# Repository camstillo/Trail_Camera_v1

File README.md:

# Trail_Camera_v1
 Schematic and ordering information for trail camera device

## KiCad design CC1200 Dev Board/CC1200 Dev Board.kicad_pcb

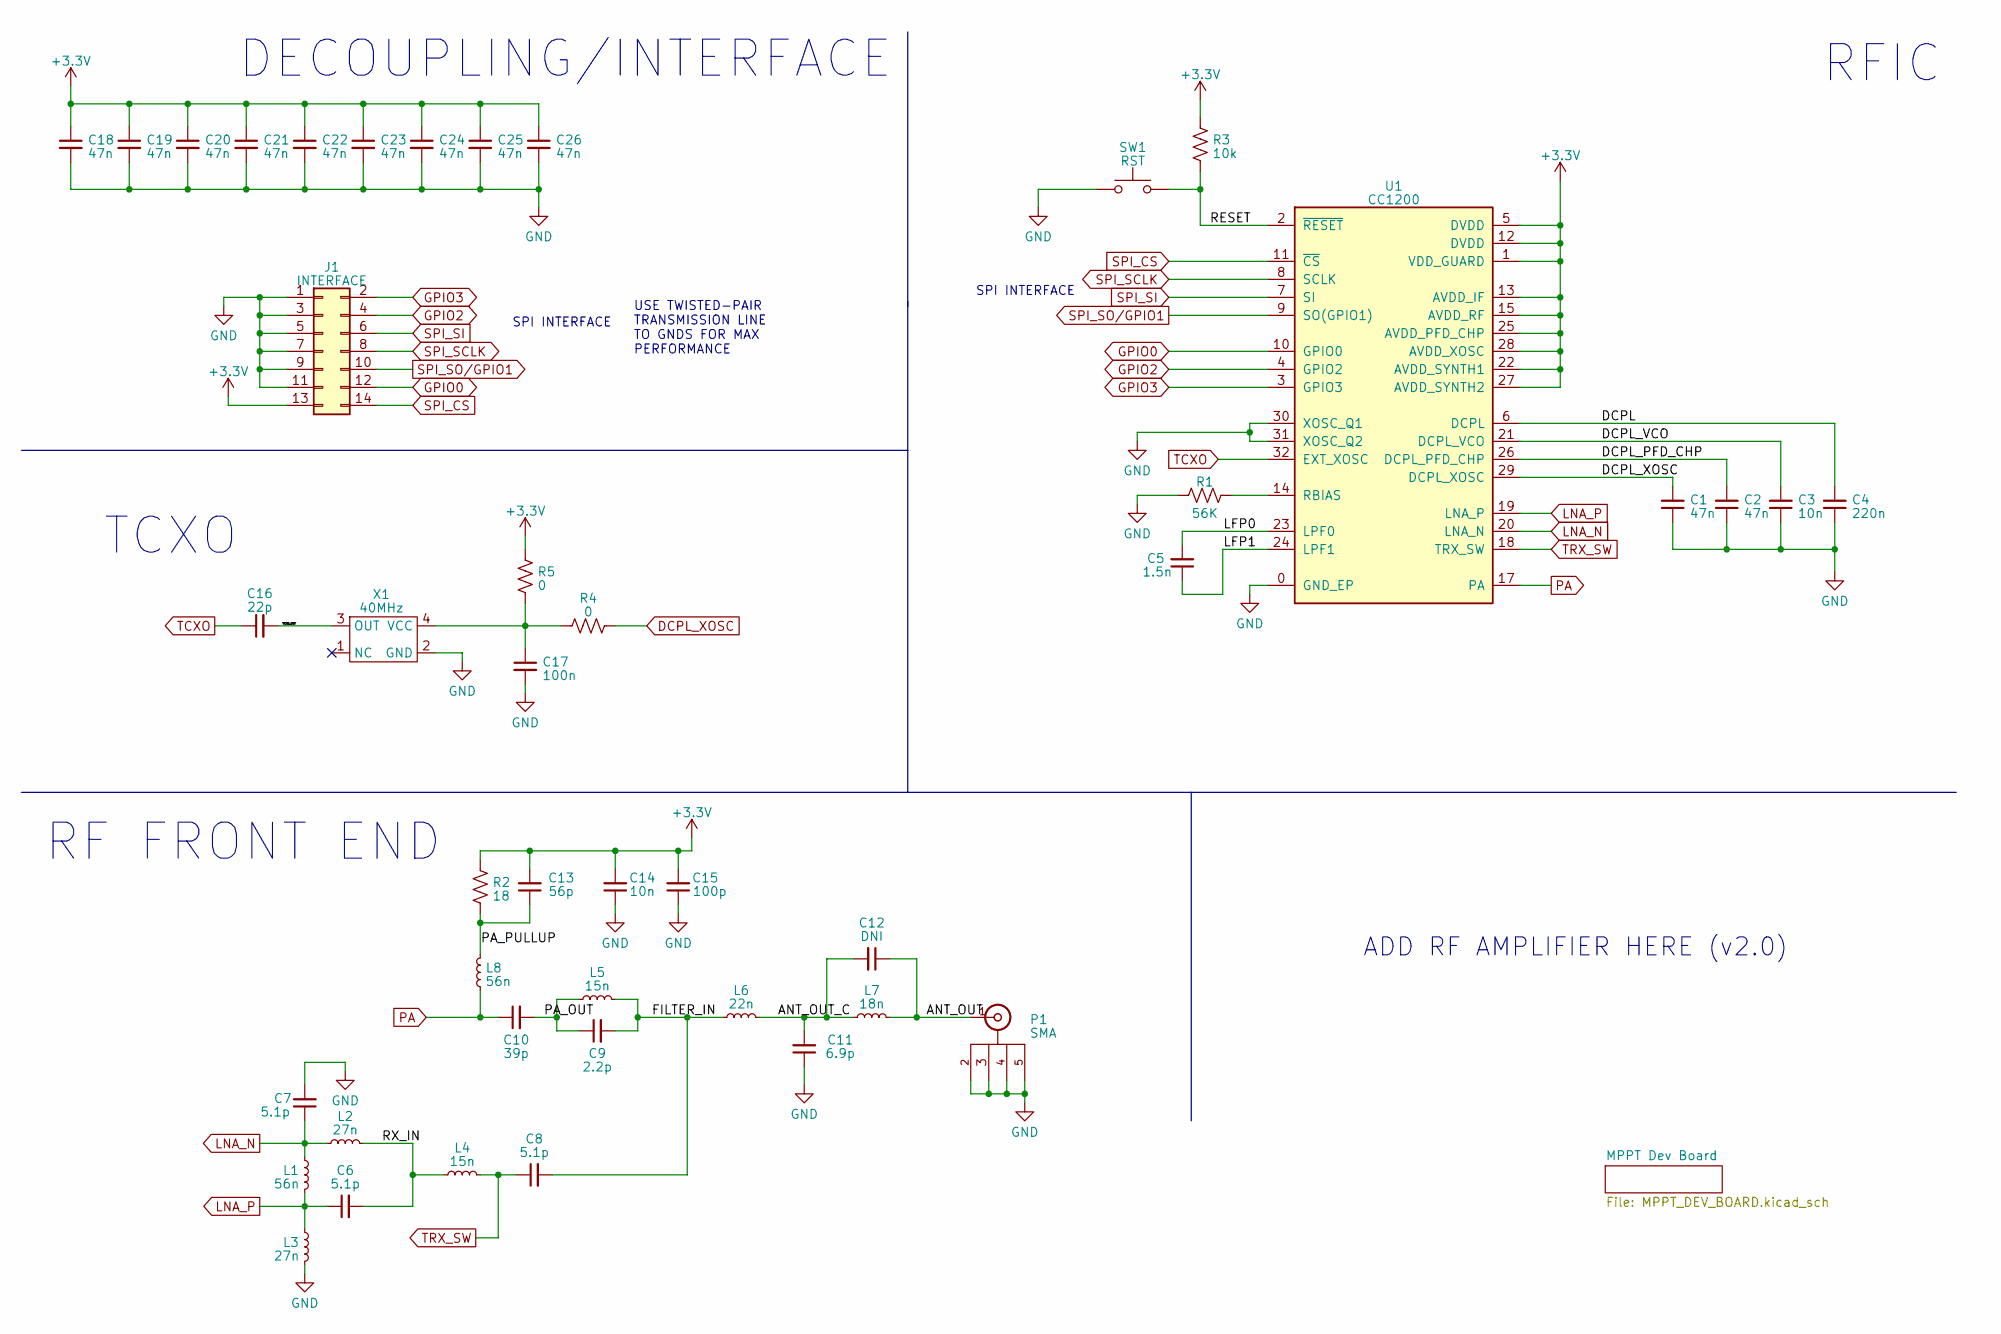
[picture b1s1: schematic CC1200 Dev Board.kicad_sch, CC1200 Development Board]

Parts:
C1, C2, C18, C19, C20, C21, C22, C23, C24, C25, C26: 47n; C_0402_1005Metric_Pad0.74x0.62mm_HandSolder
C3, C14: 10n; C_0402_1005Metric_Pad0.74x0.62mm_HandSolder
C4: 220n; C_0402_1005Metric_Pad0.74x0.62mm_HandSolder
C5: 1.5n; C_0402_1005Metric_Pad0.74x0.62mm_HandSolder
C6, C7, C8: 5.1p; C_0402_1005Metric_Pad0.74x0.62mm_HandSolder
C9: 2.2p; C_0402_1005Metric_Pad0.74x0.62mm_HandSolder
C10: 39p; C_0402_1005Metric_Pad0.74x0.62mm_HandSolder
C11: 6.9p; C_0402_1005Metric_Pad0.74x0.62mm_HandSolder
C12: DNI; C_0402_1005Metric_Pad0.74x0.62mm_HandSolder
C13: 56p; C_0402_1005Metric_Pad0.74x0.62mm_HandSolder
C15: 100p; C_0402_1005Metric_Pad0.74x0.62mm_HandSolder
C16: 22p; C_0402_1005Metric_Pad0.74x0.62mm_HandSolder
C17: 100n; C_0402_1005Metric_Pad0.74x0.62mm_HandSolder
J1: INTERFACE; PinHeader_2x07_P2.54mm_Vertical_SMD
L1, L8: 56n; L_0402_1005Metric_Pad0.77x0.64mm_HandSolder
L2, L3: 27n; L_0402_1005Metric_Pad0.77x0.64mm_HandSolder
L4, L5: 15n; L_0402_1005Metric_Pad0.77x0.64mm_HandSolder
L6: 22n; L_0402_1005Metric_Pad0.77x0.64mm_HandSolder
L7: 18n; L_0402_1005Metric_Pad0.77x0.64mm_HandSolder
P1: SMA; CONSMA001-SMD-G_ALT
R1: 56K; R_0402_1005Metric_Pad0.72x0.64mm_HandSolder
R2: 18; R_0402_1005Metric_Pad0.72x0.64mm_HandSolder
R3: 10k; R_0402_1005Metric_Pad0.72x0.64mm_HandSolder
R4, R5: 0; R_0402_1005Metric_Pad0.72x0.64mm_HandSolder
SW1: RST; PTS636 SL43 SMTR LFS
U1: CC1200
X1: 40MHz; TG2520SMN

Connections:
+3.3V: C13.2, C14.2, C15.2, C18.1, C19.1, C20.1, C21.1, C22.1, C23.1, C24.1, C25.1, C26.1, J1.13, R2.1, R3.1, R5.2, U1.1 (VDD_GUARD), U1.5 (DVDD), U1.12 (DVDD), U1.13 (AVDD_IF), U1.15 (AVDD_RF), U1.22 (AVDD_SYNTH1), U1.25 (AVDD_PFD_CHP), U1.27 (AVDD_SYNTH2), U1.28 (AVDD_XOSC)
/ANT_OUT: C12.1, L7.2, P1.1 (In); also elsewhere on the board
/ANT_OUT_C: C11.2, C12.2, L6.2, L7.1
/DCPL: C4.2, U1.6 (DCPL)
/DCPL_PFD_CHP: C2.2, U1.26 (DCPL_PFD_CHP)
/DCPL_VCO: C3.2, U1.21 (DCPL_VCO)
/FILTER_IN: C8.2, C9.2, L5.2, L6.1
/LFP0: C5.2, U1.23 (LPF0)
/LFP1: C5.1, U1.24 (LPF1)
/PA_OUT: C9.1, C10.2, L5.1
/PA_PULLUP: C13.1, L8.2, R2.2
/RESET: R3.2, SW1.2, U1.2 (~RESET); also elsewhere on the board
/RX_IN: C6.2, L2.2, L4.1
/TCXO_OUT: C16.2, X1.3 (OUT)
DCPL_XOSC: C1.2, R4.2, U1.29 (DCPL_XOSC)
GND: C1.1, C2.1, C3.1, C4.1, C7.2, C11.1, C14.1, C15.1, C17.2, C18.2, C19.2, C20.2, C21.2, C22.2, C23.2, C24.2, C25.2, C26.2, J1.1, J1.3, J1.5, J1.7, J1.9, J1.11, L3.2, P1.2 (Body), P1.3, P1.4, P1.5, R1.1, SW1.1, U1.0 (GND_EP), U1.30 (XOSC_Q1), U1.31 (XOSC_Q2), X1.2 (GND); also elsewhere on the board
GPIO0: J1.12, U1.10 (GPIO0)
GPIO2: J1.4, U1.4 (GPIO2)
GPIO3: J1.2, U1.3 (GPIO3)
LNA_N: C7.1, L1.1, L2.1, U1.20 (LNA_N)
LNA_P: C6.1, L1.2, L3.1, U1.19 (LNA_P)
MPPTSET_RST: SW1.2; also elsewhere on the board
unnamed: R1.2, U1.14 (RBIAS)
unnamed: C17.1, R4.1, R5.1, X1.4 (VCC)
PA: C10.1, L8.1, U1.17 (PA)
SPI_CS: J1.14, U1.11 (~CS)
SPI_SCLK: J1.8, U1.8 (SCLK)
SPI_SI: J1.6, U1.7 (SI)
SPI_SO/GPIO1: J1.10, U1.9 (SO(GPIO1))
TCXO: C16.1, U1.32 (EXT_XOSC)
TRX_SW: C8.1, L4.2, U1.18 (TRX_SW)

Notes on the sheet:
RFIC
TCXO
RF FRONT END
ADD RF AMPLIFIER HERE (v2.0)
DECOUPLING/INTERFACE
USE TWISTED-PAIR TRANSMISSION LINE TO GNDS FOR MAX PERFORMANCE
SPI INTERFACE

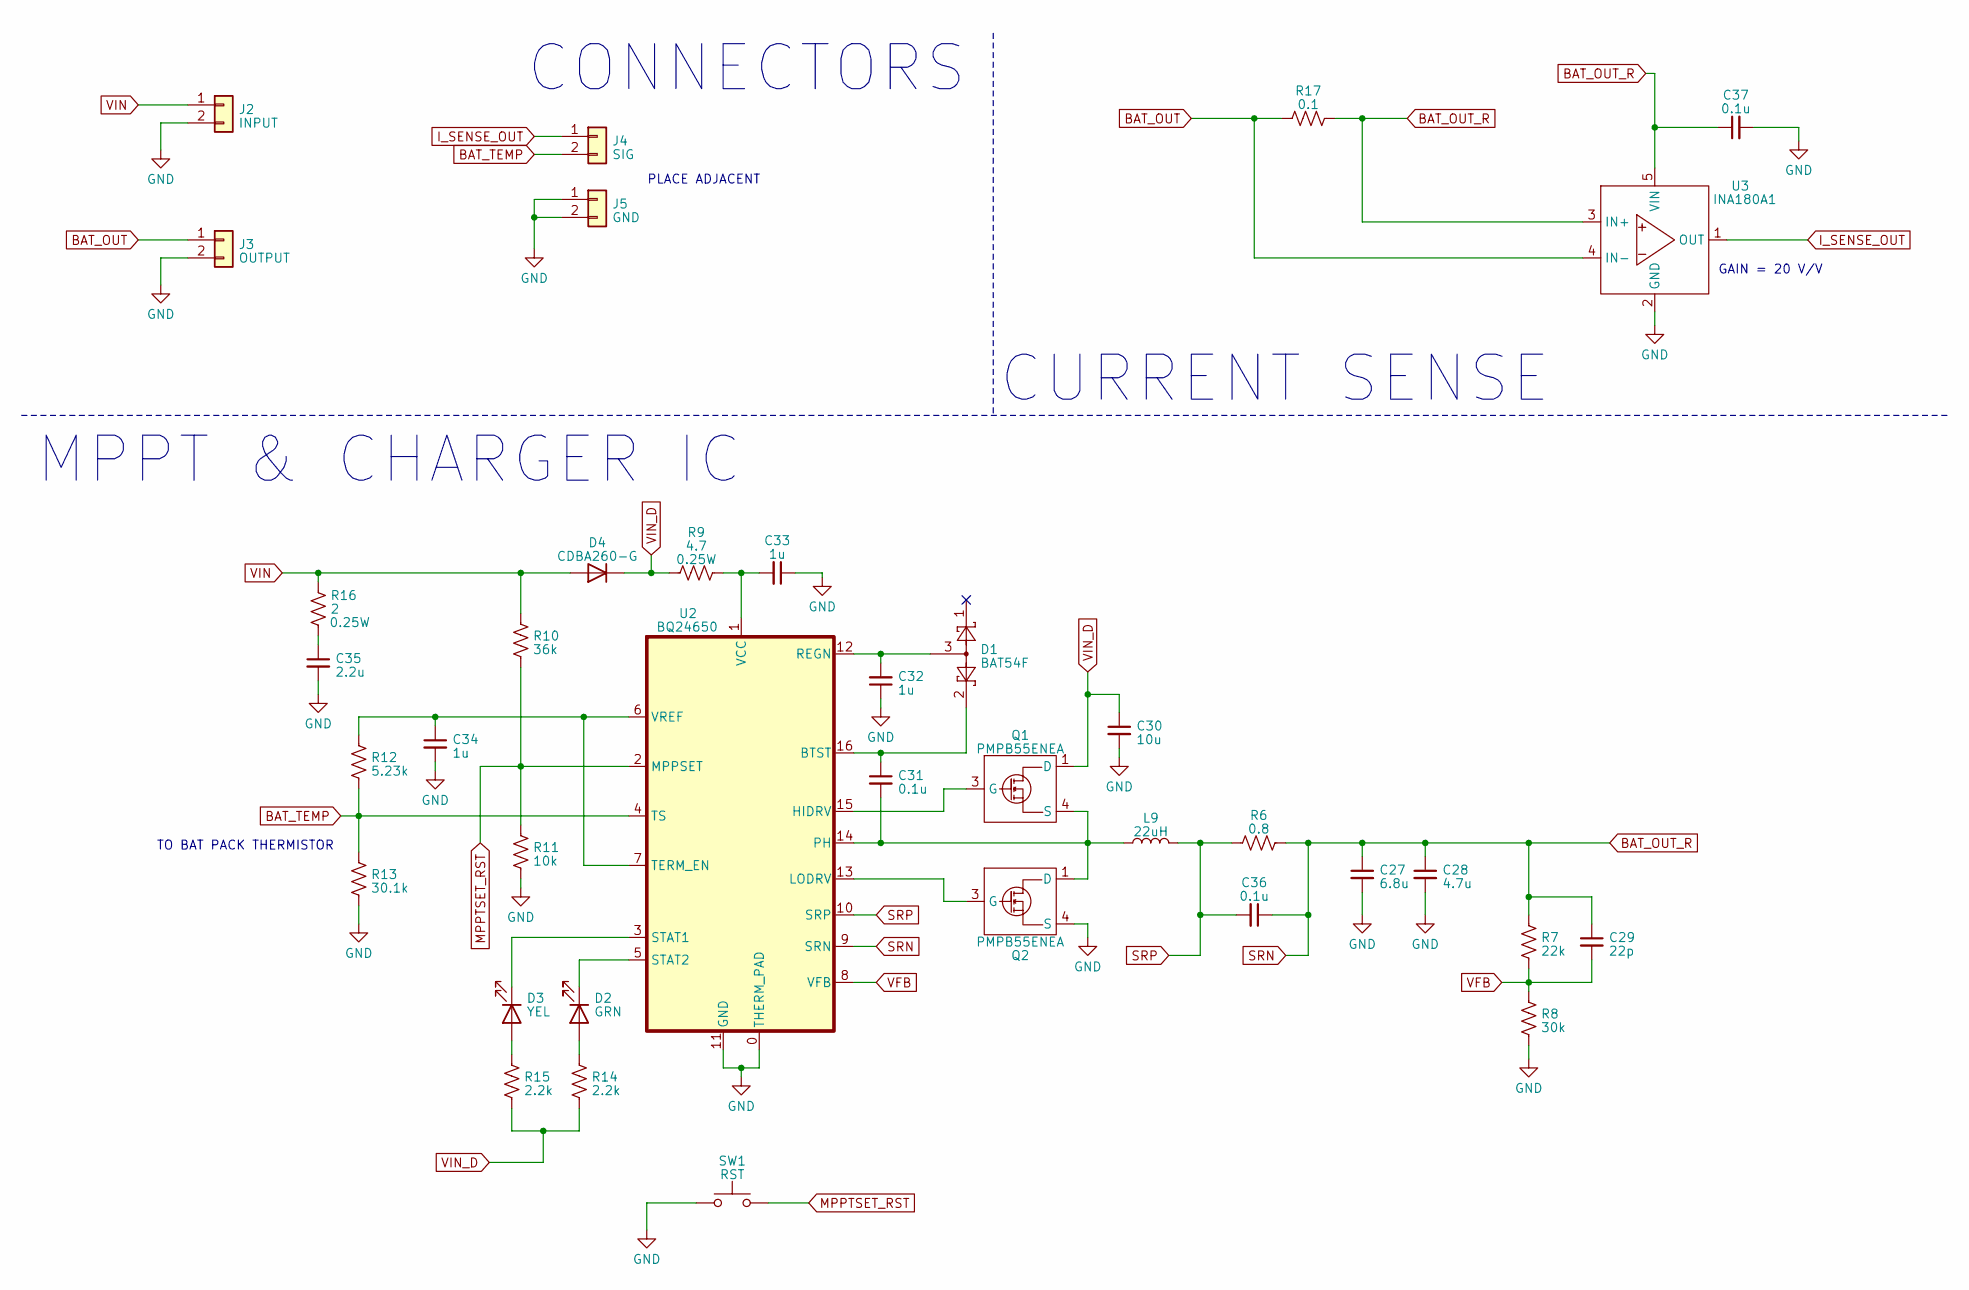
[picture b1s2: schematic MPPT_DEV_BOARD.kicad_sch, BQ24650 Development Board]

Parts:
C27: 6.8u; C_1206_3216Metric
C28: 4.7u; C_1206_3216Metric
C29: 22p; C_0402_1005Metric_Pad0.74x0.62mm_HandSolder
C30: 10u; C_0603_1608Metric
C31, C36, C37: 0.1u; C_0402_1005Metric_Pad0.74x0.62mm_HandSolder
C32, C33, C34: 1u; C_0402_1005Metric_Pad0.74x0.62mm_HandSolder
C35: 2.2u; C_0603_1608Metric
D1: BAT54F; BAT54-7-F
D2: GRN; MSAST105SB5104KFNA01
D3: YEL; MSAST105SB5104KFNA01
D4: CDBA260-G
J2: INPUT; InOut_Pads
J3: OUTPUT; InOut_Pads
J4: SIG; InOut_Pads
J5: GND; InOut_Pads
L9: 22uH; SRR1005-220Y
Q1, Q2: PMPB55ENEA
R6: 0.8; R_1206_3216Metric
R7: 22k; R_0402_1005Metric_Pad0.72x0.64mm_HandSolder
R8: 30k; R_0402_1005Metric_Pad0.72x0.64mm_HandSolder
R9: 4.7; R_1206_3216Metric
R10: 36k; R_0402_1005Metric_Pad0.72x0.64mm_HandSolder
R11: 10k; R_0402_1005Metric_Pad0.72x0.64mm_HandSolder
R12: 5.23k; R_0402_1005Metric_Pad0.72x0.64mm_HandSolder
R13: 30.1k; R_0402_1005Metric_Pad0.72x0.64mm_HandSolder
R14, R15: 2.2k; R_0402_1005Metric_Pad0.72x0.64mm_HandSolder
R16: 2; R_1206_3216Metric
R17: 0.1; R_0603_1608Metric
SW1: RST; PTS636 SL43 SMTR LFS
U2: BQ24650
U3: INA180A1; INA180A1IDBVR

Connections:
/RESET: SW1.2; also elsewhere on the board
BAT_OUT: J3.1, R17.1, U3.4 (IN-)
BAT_OUT_R: C27.1, C28.1, C29.1, C36.1, C37.1, R6.2, R7.2, R17.2, U2.9 (SRN), U3.3 (IN+), U3.5 (VIN)
BAT_TEMP: J4.2, R12.1, R13.2, U2.4 (TS)
GND: C27.2, C28.2, C30.2, C32.1, C33.1, C34.2, C35.2, C37.2, J2.2, J3.2, J5.1, J5.2, Q2.4 (S), Q2.8 (S), R8.1, R11.1, R13.1, SW1.1, U2.0 (THERM_PAD), U2.11 (GND), U3.2 (GND); also elsewhere on the board
I_SENSE_OUT: J4.1, U3.1 (OUT)
MPPTSET_RST: R10.1, R11.2, SW1.2, U2.2 (MPPSET); also elsewhere on the board
unnamed: C35.1, R16.1
unnamed: D2.2 (A), R14.2
unnamed: D2.1 (K), U2.5 (STAT2)
unnamed: D3.2 (A), R15.2
unnamed: D3.1 (K), U2.3 (STAT1)
unnamed: Q1.3 (G), U2.15 (HIDRV)
unnamed: Q2.3 (G), U2.13 (LODRV)
unnamed: C31.1, D1.2, U2.16 (BTST)
unnamed: C31.2, L9.1, Q1.4 (S), Q1.8 (S), Q2.1 (D), Q2.2 (D), Q2.5 (D), Q2.6 (D), Q2.7 (D), U2.14 (PH)
unnamed: C32.2, D1.3, U2.12 (REGN)
unnamed: C34.1, R12.2, U2.6 (VREF), U2.7 (TERM_EN)
unnamed: C33.2, R9.2, U2.1 (VCC)
SRP: C36.2, L9.2, R6.1, U2.10 (SRP)
VFB: C29.2, R7.1, R8.2, U2.8 (VFB)
VIN: D4.2 (A), J2.1, R10.2, R16.2
VIN_D: C30.1, D4.1 (K), Q1.1 (D), Q1.2 (D), Q1.5 (D), Q1.6 (D), Q1.7 (D), R9.1, R14.1, R15.1

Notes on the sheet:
MPPT & CHARGER IC
PLACE ADJACENT
GAIN = 20 V/V
CURRENT SENSE
CONNECTORS
TO BAT PACK THERMISTOR

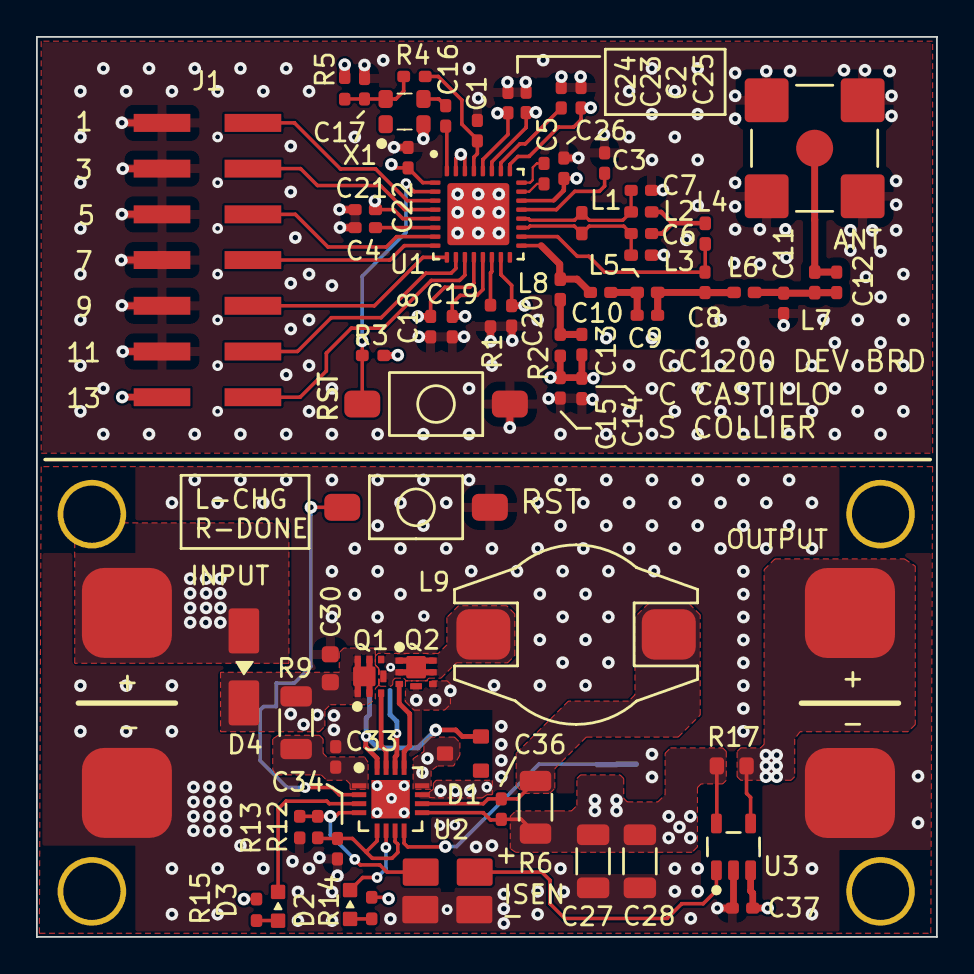
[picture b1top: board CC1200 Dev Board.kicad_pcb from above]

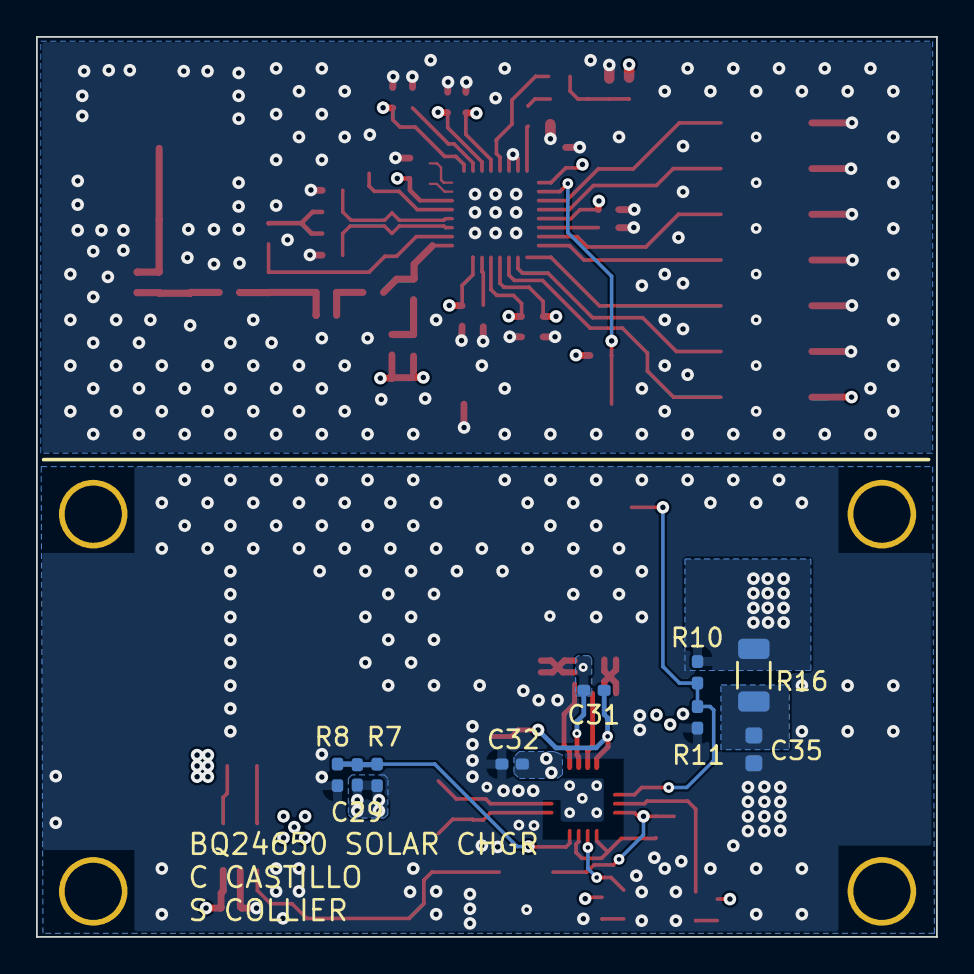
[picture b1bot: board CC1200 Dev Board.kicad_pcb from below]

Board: 4 copper layers, 50.0 x 50.0 mm, 81 parts (9 on the bottom side), 51 nets.

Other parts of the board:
ANT: SMA; CONSMA001-SMD-G_ALT
RST: RST; PTS636 SL43 SMTR LFS
RST#2: RST; PTS636 SL43 SMTR LFS

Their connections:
/ANT_OUT: ANT.1 (In); also elsewhere on the board
/RESET: RST#2.2; also elsewhere on the board
GND: ANT.2 (Body), ANT.3, ANT.4, ANT.5, RST.1, RST#2.1; also elsewhere on the board
MPPTSET_RST: RST.2; also elsewhere on the board

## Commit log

2024-01-25 Added all schematic files
2024-01-31 Added and cut some gerbers
